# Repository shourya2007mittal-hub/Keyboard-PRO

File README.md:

# Keyboard-PRO

I have building a 65% layout keyboard and it is  based on Seed Studio Xiao nrf52840 because it has Bluetooth capabilities. the number of available pins on Xiao was less So I used 2 expanders for connection . <br>The keyboard also has a  3.7v battery for the power also it could be charged by the USB-C available on xiao as it has an inbuilt charging IC. <br> The keyboard also has an 0.91 inch OLED Screen . Which will be used to display present time/ and how long are you working for . <br> The  Switches  on the board are also hot swappable. So there is no need to solder the switches and we could easily change it .    <br> The board also include a micro pad of 4x3 layout which could be used as shot-cuts for any apps  and has 3 rotor encoders to control volume/Brightness/ timeline (while editing/ Zoom in-out).

<br> The CAD design is a three layered design in which the Bottom layer holds the keyboard PCB and there is a middle layer holds and give structure to the Switches and stabilizes them . then the top layer close and finished the board. All the three pieces connect to each other in a leg-joint manner. 
<br>

## Features
-  nrf52840 Rp2040
- uses 65% Keyboard Layout 
-  Uses Keyboard Matrix
-  Had a rotor encoder and an 0.91 inch oled screen
-  had a 4x3 layout MicroPad

  | Item | Price | Source |
| :--- | :---: | :--- |
| PCB + Shipping - Coupons | 28.74 | JLCPCB |
| KeyCaps | 15.04 | [Meckeys Link](https://meckeys.com/shop/accessories/keyboard-accessories/keycaps/gengar-anime-keycap-set/) |
| Hot-swap (pack of 10) x7 | 5.20 | [Meckeys Link](https://meckeys.com/shop/accessories/keyboard-accessories/key-switches/kailh-hot-swap-socket/?attribute_pa_variations=white) |
| Switches (pack of 10) x 8 | 25.20 | [Meckeys Link](https://meckeys.com/shop/accessories/keyboard-accessories/key-switches/hmx-xinhai-switch/?attribute_pa_key-switches=hmx-xinhai-45g) |
| Stabilizers | 10.76 | [Meckeys Link](https://meckeys.com/shop/accessories/keyboard-accessories/more/glorious-goat-stabilizers/) |
| Meckey shipping | 1.10 | meckeys.com |
| Expander x 2 | 6.22 | [Robu Link](https://robu.in/product/pca9555dwr-texas-instruments-400khz-soic-24-300mil-i-o-expanders-rohs/) |
| XIAO BLE nRF52840 | 12.40 | [Robu Link](https://robu.in/product/seeed-studio-xiao-ble-nrf52840/) |
| 0.91 OLED | 1.93 | [Robu Link](https://robu.in/product/blue-oled-display-module/) |
| Rotor Encoder x 3 | 1.36 | [Robu Link](https://robu.in/product/m274-360-degree-rotary-encoder-module-brick-sensor/?gad_source=1&gad_campaignid=20363337560&gbraid=0AAAAADvLFWcBh7394q4T97b_tz-uHZen0&gclid=Cj0KCQjw4orUBhCjARIsAIbF3qxV2X32v_dV24K8ymAecPKpoQ2W7oZQI5S6fIRl1lJOTUxK9ed91Z0aAgdcEALw_wcB) |
| On-Off switch | 1.12 | [Robu Link](https://robu.in/product/os202011ma0qn1-ck-100ma-dpdt-12v-10000-times-plugin-slide-switches-rohs/) |
| 2M OHM Resistor | 0.13 | [Robu Link](https://robu.in/product/crcw12062m20fkea-vishay-smd-chip-resistor-2-2-mohm-%c2%b1-1-250-mw-1206-3216-metric-thick-film-general-purpose/) |
| 806k resistor | 0.13 | [Robu Link](https://robu.in/product/rc0402fr-07806kl-yageo-smd-chip-resistor-806-kohm-%c2%b1-1-63-mw-0402-1005-metric-thick-film-general-purpose/) |
| Robu shipping | 1.10 | robu.in |
| Solder Paste for SMD components | 2.70 | [Amazon Link](https://www.amazon.in/gp/product/B0GY879KCL/ref=ox_sc_act_title_1?smid=A2TAUOL95KBX1X&psc=1) |
| 1N4148W-T4 diodes (Pack of 15) X 5 *(used Amazon because non-available elsewhere)* | 11.78 | [Amazon Link](https://www.amazon.in/gp/product/B0FZL2D1GG/ref=ox_sc_act_title_2?smid=A28WR0HSDEABON&psc=1) |
| **Total** | **124.91** | |

### Schematic<br><br>

###  PCB Design<br><br>

### 3D Render <br><br>

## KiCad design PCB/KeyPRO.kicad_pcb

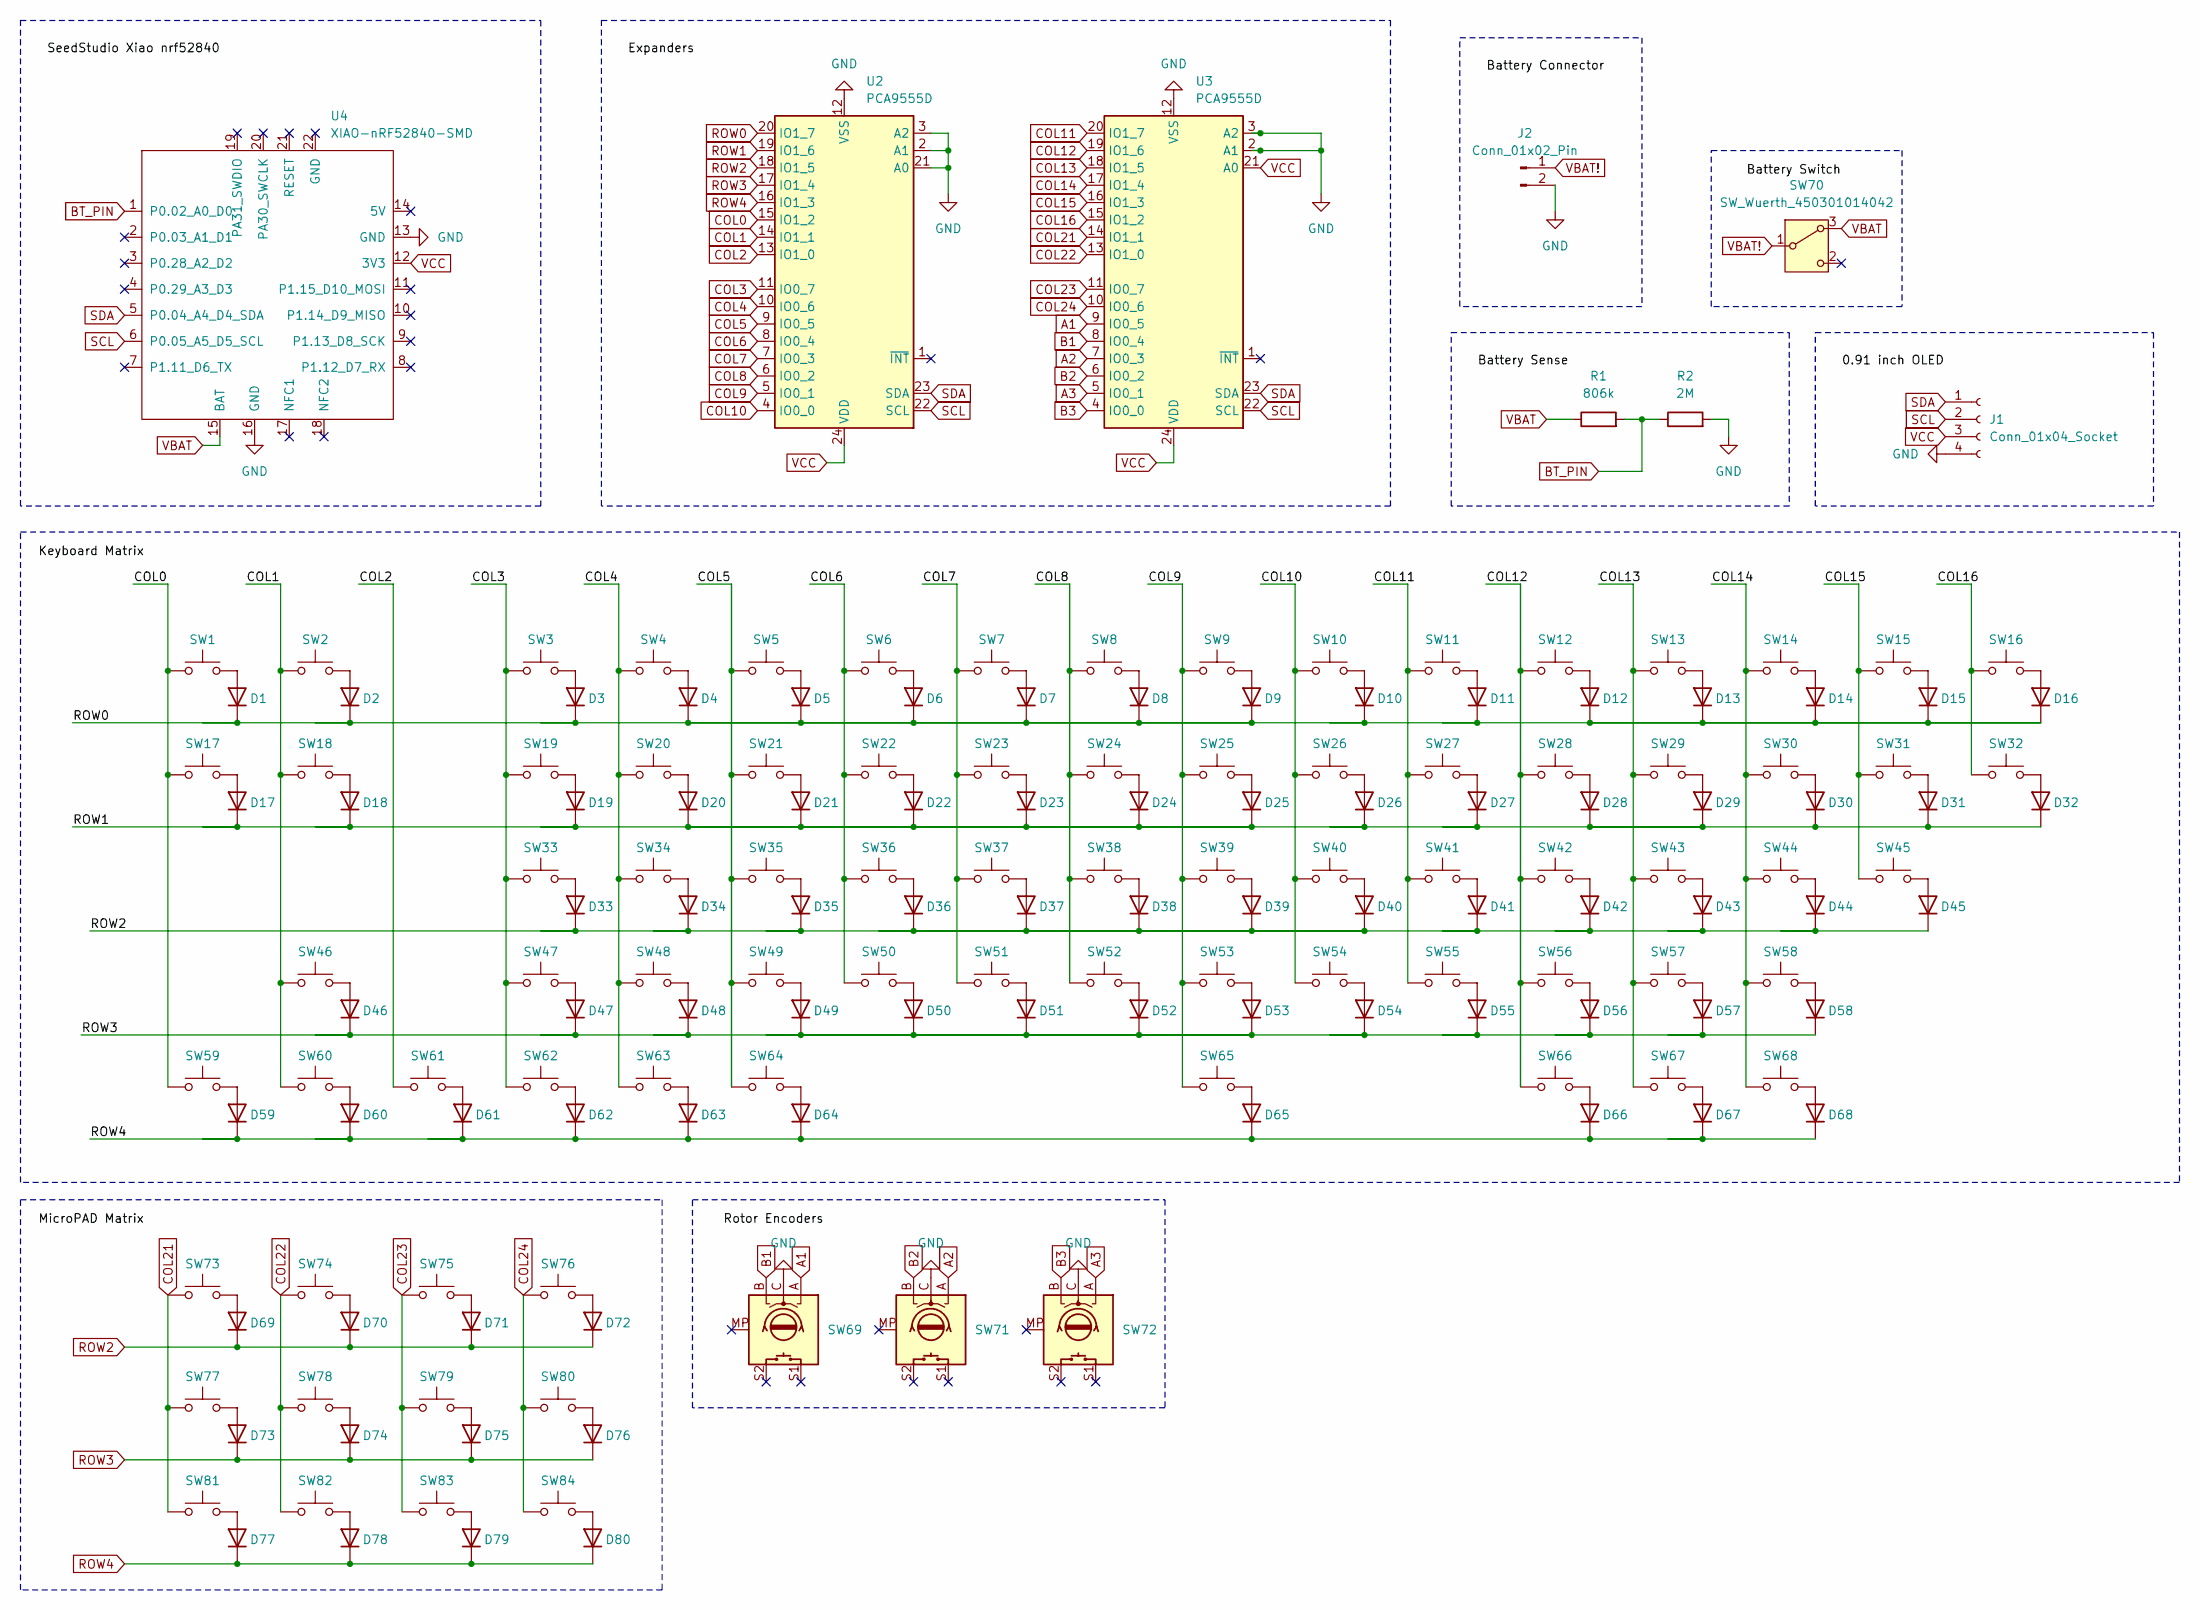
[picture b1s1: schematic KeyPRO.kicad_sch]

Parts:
D1, D2, D3, D4, D5, D6, D7, D8, D9, D10, D11, D12, D13, D14, D15, D16, D17, D18, D19, D20, D21, D22, D23, D24, D25, D26, D27, D28, D29, D30, D31, D32, D33, D34, D35, D36, D37, D38, D39, D40, D41, D42, D43, D44, D45, D46, D47, D48, D49, D50, D51, D52, D53, D54, D55, D56, D57, D58, D59, D60, D61, D62, D63, D64, D65, D66, D67, D68, D69, D70, D71, D72, D73, D74, D75, D76, D77, D78, D79, D80: D; D_SOD-123
J1: Conn_01x04_Socket; PinHeader_1x04_P2.54mm_Vertical
J2: Conn_01x02_Pin; JST_JWPF_B02B-JWPF-SK-R_1x02_P2.00mm_Vertical
R1: 806k; R_0805_2012Metric
R2: 2M; R_0805_2012Metric
SW1, SW2, SW3, SW4, SW5, SW6, SW7, SW8, SW9, SW10, SW11, SW12, SW13, SW14, SW15, SW16, SW17, SW18, SW19, SW20, SW21, SW22, SW23, SW24, SW25, SW26, SW27, SW28, SW29, SW30, SW31, SW32, SW33, SW34, SW35, SW36, SW37, SW38, SW39, SW40, SW41, SW42, SW43, SW44, SW45, SW46, SW47, SW48, SW49, SW50, SW51, SW52, SW53, SW54, SW55, SW56, SW57, SW58, SW59, SW60, SW61, SW62, SW63, SW64, SW65, SW66, SW67, SW68: SW_Push; SW_MX_HS_CPG151101S11_1u
SW69, SW71, SW72: RotaryEncoder_Switch_MP; RotaryEncoder_Alps_EC11E-Switch_Vertical_H20mm
SW70: SW_Wuerth_450301014042; SW_Slide_SPDT_Straight_CK_OS102011MS2Q
SW73, SW74, SW75, SW76, SW77, SW78, SW79, SW80, SW81, SW82, SW83, SW84: SW_Push; SW_Cherry_MX_1.00u_PCB
U2, U3: PCA9555D; SOIC-24W_7.5x15.4mm_P1.27mm
U4: XIAO-nRF52840-SMD; modified-XIAO-nRF52840-SMD

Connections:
A1: SW69.A, U3.9 (IO0_5)
A2: SW71.A, U3.7 (IO0_3)
A3: SW72.A, U3.5 (IO0_1)
B1: SW69.B, U3.8 (IO0_4)
B2: SW71.B, U3.6 (IO0_2)
B3: SW72.B, U3.4 (IO0_0)
BT_PIN: R1.2, R2.1, U4.1 (P0.02_A0_D0)
COL0: SW1.1, SW17.1, SW59.1, U2.15 (IO1_2)
COL1: SW2.1, SW18.1, SW46.1, SW60.1, U2.14 (IO1_1)
COL2: SW61.1, U2.13 (IO1_0)
COL3: SW3.1, SW19.1, SW33.1, SW47.1, SW62.1, U2.11 (IO0_7)
COL4: SW4.1, SW20.1, SW34.1, SW48.1, SW63.1, U2.10 (IO0_6)
COL5: SW5.1, SW21.1, SW35.1, SW49.1, SW64.1, U2.9 (IO0_5)
COL6: SW6.1, SW22.1, SW36.1, SW50.1, U2.8 (IO0_4)
COL7: SW7.1, SW23.1, SW37.1, SW51.1, U2.7 (IO0_3)
COL8: SW8.1, SW24.1, SW38.1, SW52.1, U2.6 (IO0_2)
COL9: SW9.1, SW25.1, SW39.1, SW53.1, SW65.1, U2.5 (IO0_1)
COL10: SW10.1, SW26.1, SW40.1, SW54.1, U2.4 (IO0_0)
COL11: SW11.1, SW27.1, SW41.1, SW55.1, U3.20 (IO1_7)
COL12: SW12.1, SW28.1, SW42.1, SW56.1, SW66.1, U3.19 (IO1_6)
COL13: SW13.1, SW29.1, SW43.1, SW57.1, SW67.1, U3.18 (IO1_5)
COL14: SW14.1, SW30.1, SW44.1, SW58.1, SW68.1, U3.17 (IO1_4)
COL15: SW15.1, SW31.1, SW45.1, U3.16 (IO1_3)
COL16: SW16.1, SW32.1, U3.15 (IO1_2)
COL21: SW73.1, SW77.1, SW81.1, U3.14 (IO1_1)
COL22: SW74.1, SW78.1, SW82.1, U3.13 (IO1_0)
COL23: SW75.1, SW79.1, SW83.1, U3.11 (IO0_7)
COL24: SW76.1, SW80.1, SW84.1, U3.10 (IO0_6)
GND: J1.4, J2.2, R2.2, SW69.C, SW71.C, SW72.C, U2.2 (A1), U2.3 (A2), U2.12 (VSS), U2.21 (A0), U3.2 (A1), U3.3 (A2), U3.12 (VSS), U4.13 (GND), U4.16 (GND)
unnamed: D1.2 (A), SW1.2
unnamed: D2.2 (A), SW2.2
unnamed: D3.2 (A), SW3.2
unnamed: D4.2 (A), SW4.2
unnamed: D5.2 (A), SW5.2
unnamed: D6.2 (A), SW6.2
unnamed: D7.2 (A), SW7.2
unnamed: D8.2 (A), SW8.2
unnamed: D9.2 (A), SW9.2
unnamed: D10.2 (A), SW10.2
unnamed: D11.2 (A), SW11.2
unnamed: D12.2 (A), SW12.2
unnamed: D13.2 (A), SW13.2
unnamed: D14.2 (A), SW14.2
unnamed: D15.2 (A), SW15.2
unnamed: D16.2 (A), SW16.2
unnamed: D17.2 (A), SW17.2
unnamed: D18.2 (A), SW18.2
unnamed: D19.2 (A), SW19.2
unnamed: D20.2 (A), SW20.2
unnamed: D21.2 (A), SW21.2
unnamed: D22.2 (A), SW22.2
unnamed: D23.2 (A), SW23.2
unnamed: D24.2 (A), SW24.2
unnamed: D25.2 (A), SW25.2
unnamed: D26.2 (A), SW26.2
unnamed: D27.2 (A), SW27.2
unnamed: D28.2 (A), SW28.2
unnamed: D29.2 (A), SW29.2
unnamed: D30.2 (A), SW30.2
unnamed: D31.2 (A), SW31.2
unnamed: D32.2 (A), SW32.2
unnamed: D33.2 (A), SW33.2
unnamed: D34.2 (A), SW34.2
unnamed: D35.2 (A), SW35.2
unnamed: D36.2 (A), SW36.2
unnamed: D37.2 (A), SW37.2
unnamed: D38.2 (A), SW38.2
unnamed: D39.2 (A), SW39.2
unnamed: D40.2 (A), SW40.2
unnamed: D41.2 (A), SW41.2
unnamed: D42.2 (A), SW42.2
unnamed: D43.2 (A), SW43.2
unnamed: D44.2 (A), SW44.2
unnamed: D45.2 (A), SW45.2
unnamed: D46.2 (A), SW46.2
unnamed: D47.2 (A), SW47.2
unnamed: D48.2 (A), SW48.2
unnamed: D49.2 (A), SW49.2
unnamed: D50.2 (A), SW50.2
unnamed: D51.2 (A), SW51.2
unnamed: D52.2 (A), SW52.2
unnamed: D53.2 (A), SW53.2
unnamed: D54.2 (A), SW54.2
unnamed: D55.2 (A), SW55.2
unnamed: D56.2 (A), SW56.2
unnamed: D57.2 (A), SW57.2
unnamed: D58.2 (A), SW58.2
unnamed: D59.2 (A), SW59.2
unnamed: D60.2 (A), SW60.2
unnamed: D61.2 (A), SW61.2
unnamed: D62.2 (A), SW62.2
unnamed: D63.2 (A), SW63.2
unnamed: D64.2 (A), SW64.2
unnamed: D65.2 (A), SW65.2
unnamed: D66.2 (A), SW66.2
unnamed: D67.2 (A), SW67.2
unnamed: D68.2 (A), SW68.2
unnamed: D69.2 (A), SW73.2
unnamed: D70.2 (A), SW74.2
unnamed: D71.2 (A), SW75.2
unnamed: D72.2 (A), SW76.2
unnamed: D73.2 (A), SW77.2
unnamed: D74.2 (A), SW78.2
unnamed: D75.2 (A), SW79.2
unnamed: D76.2 (A), SW80.2
unnamed: D77.2 (A), SW81.2
unnamed: D78.2 (A), SW82.2
unnamed: D79.2 (A), SW83.2
unnamed: D80.2 (A), SW84.2
ROW0: D1.1 (K), D2.1 (K), D3.1 (K), D4.1 (K), D5.1 (K), D6.1 (K), D7.1 (K), D8.1 (K), D9.1 (K), D10.1 (K), D11.1 (K), D12.1 (K), D13.1 (K), D14.1 (K), D15.1 (K), D16.1 (K), U2.20 (IO1_7)
ROW1: D17.1 (K), D18.1 (K), D19.1 (K), D20.1 (K), D21.1 (K), D22.1 (K), D23.1 (K), D24.1 (K), D25.1 (K), D26.1 (K), D27.1 (K), D28.1 (K), D29.1 (K), D30.1 (K), D31.1 (K), D32.1 (K), U2.19 (IO1_6)
ROW2: D33.1 (K), D34.1 (K), D35.1 (K), D36.1 (K), D37.1 (K), D38.1 (K), D39.1 (K), D40.1 (K), D41.1 (K), D42.1 (K), D43.1 (K), D44.1 (K), D45.1 (K), D69.1 (K), D70.1 (K), D71.1 (K), D72.1 (K), U2.18 (IO1_5)
ROW3: D46.1 (K), D47.1 (K), D48.1 (K), D49.1 (K), D50.1 (K), D51.1 (K), D52.1 (K), D53.1 (K), D54.1 (K), D55.1 (K), D56.1 (K), D57.1 (K), D58.1 (K), D73.1 (K), D74.1 (K), D75.1 (K), D76.1 (K), U2.17 (IO1_4)
ROW4: D59.1 (K), D60.1 (K), D61.1 (K), D62.1 (K), D63.1 (K), D64.1 (K), D65.1 (K), D66.1 (K), D67.1 (K), D68.1 (K), D77.1 (K), D78.1 (K), D79.1 (K), D80.1 (K), U2.16 (IO1_3)
SCL: J1.2, U2.22 (SCL), U3.22 (SCL), U4.6 (P0.05_A5_D5_SCL)
SDA: J1.1, U2.23 (SDA), U3.23 (SDA), U4.5 (P0.04_A4_D4_SDA)
VBAT: R1.1, SW70.3 (A), U4.15 (BAT)
VBAT!: J2.1, SW70.1 (B)
VCC: J1.3, U2.24 (VDD), U3.21 (A0), U3.24 (VDD), U4.12 (3V3)

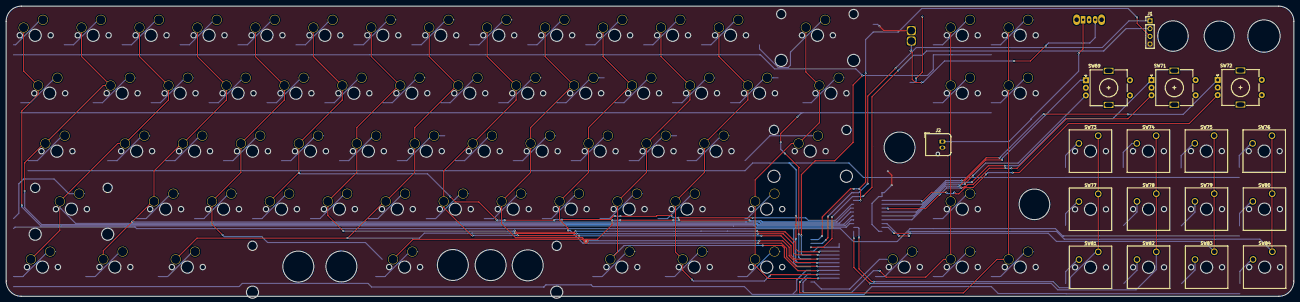
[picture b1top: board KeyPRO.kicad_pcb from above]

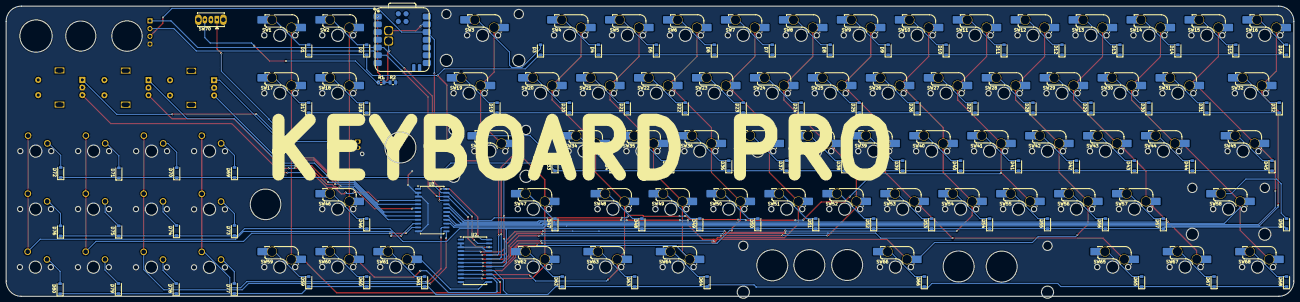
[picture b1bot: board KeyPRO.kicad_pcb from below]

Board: 2 copper layers, 423.4 x 95.4 mm, 175 parts (154 on the bottom side), 119 nets.

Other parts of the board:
S1: STAB_MX_2u
S2, S3: STAB_MX_2.25u
S4: STAB_MX_6.25u
